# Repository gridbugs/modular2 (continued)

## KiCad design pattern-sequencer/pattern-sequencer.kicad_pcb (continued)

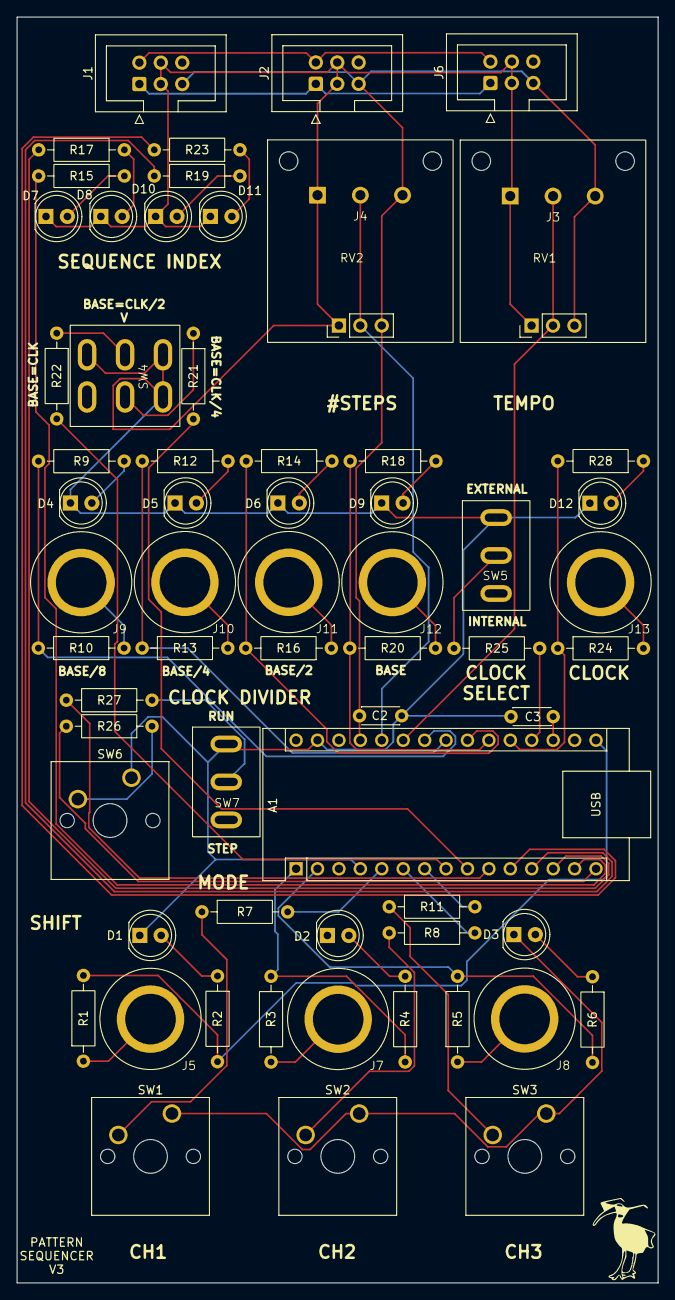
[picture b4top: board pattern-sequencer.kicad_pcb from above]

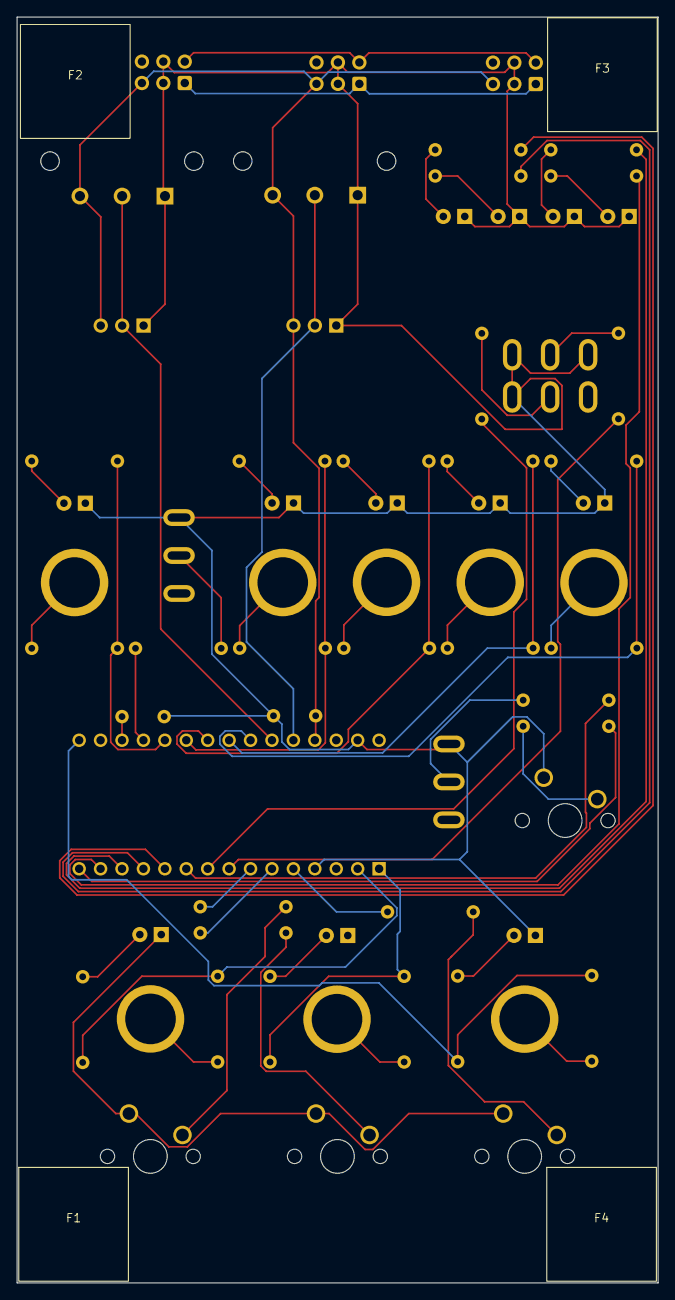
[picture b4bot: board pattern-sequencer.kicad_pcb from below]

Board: 2 copper layers, 76.0 x 150.1 mm, 69 parts (4 on the bottom side), 55 nets.

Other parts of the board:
F1, F2, F3, F4: foot

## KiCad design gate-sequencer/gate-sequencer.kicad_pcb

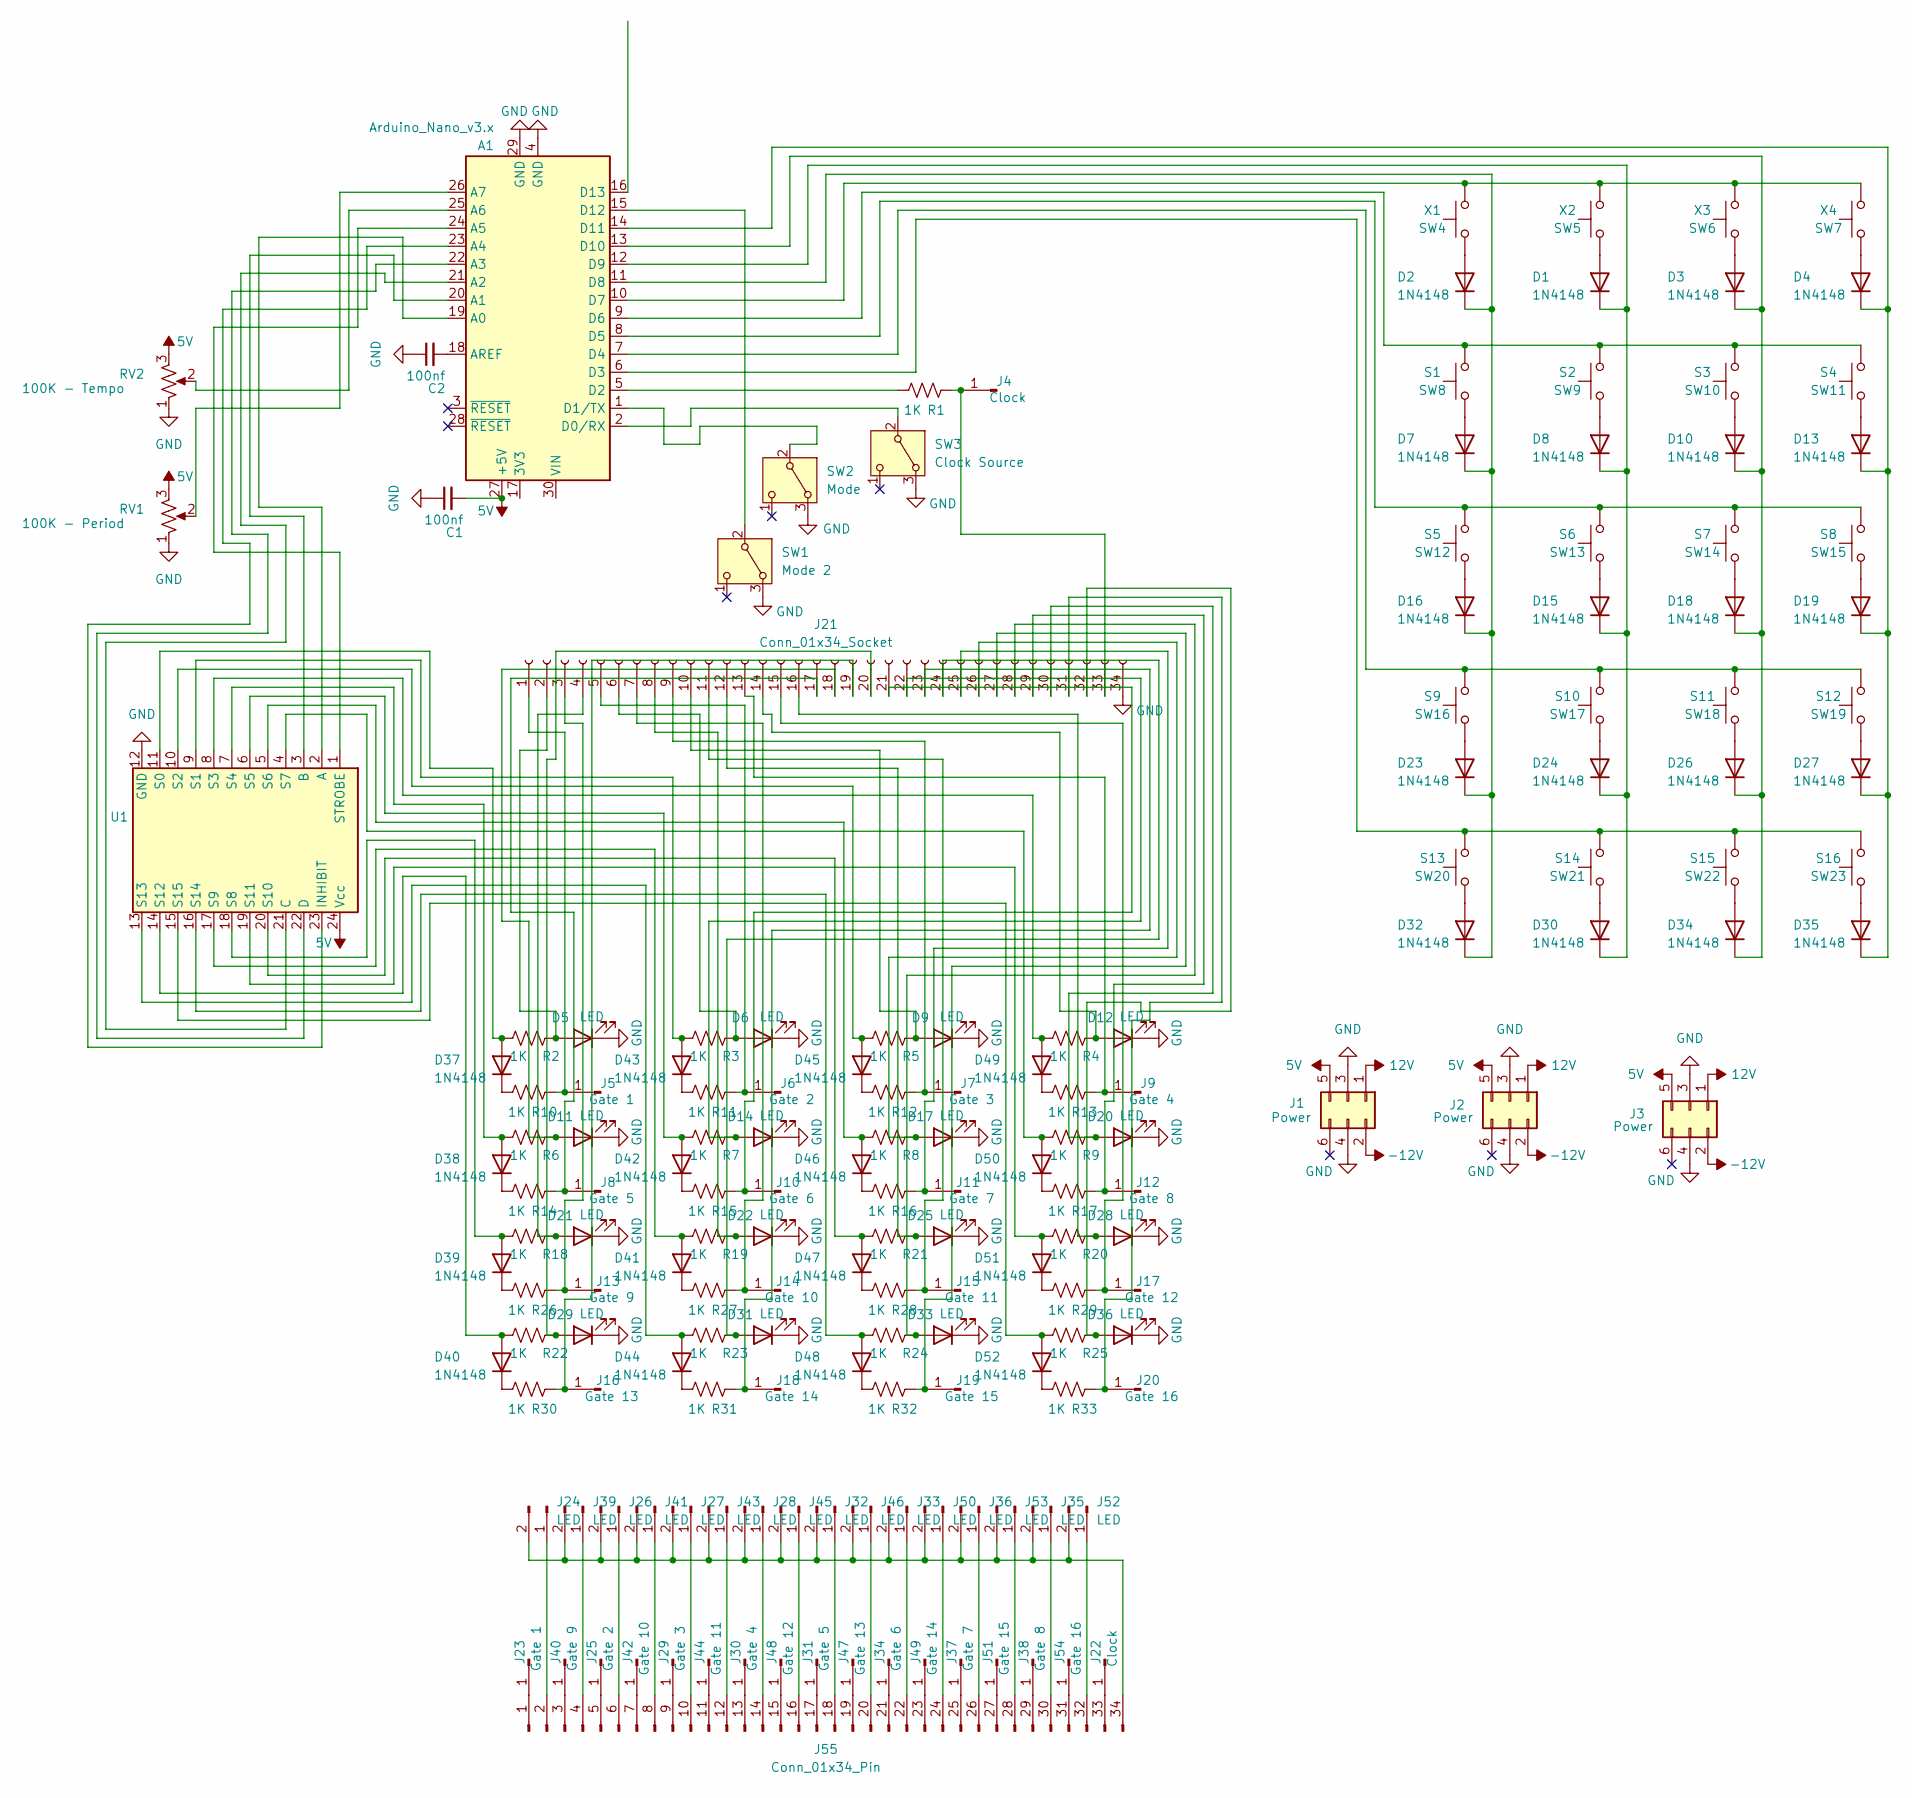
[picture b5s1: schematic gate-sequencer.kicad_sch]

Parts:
A1: Arduino_Nano_v3.x; Arduino_Nano
C1, C2: 100nf; C_Disc_D4.3mm_W1.9mm_P5.00mm
D1, D2, D3, D4, D7, D8, D10, D13, D15, D16, D18, D19, D23, D24, D26, D27, D30, D32, D34, D35, D37, D38, D39, D40, D41, D42, D43, D44, D45, D46, D47, D48, D49, D50, D51, D52: 1N4148; D_DO-35_SOD27_P7.62mm_Horizontal
D5, D6, D9, D11, D12, D14, D17, D20, D21, D22, D25, D28, D29, D31, D33, D36: LED; LED_D5.0mm
J1, J2, J3: Power; IDC-Header_2x03_P2.54mm_Vertical
J4, J22: Clock; banana-jack
J5, J23: Gate 1; banana-jack
J6, J25: Gate 2; banana-jack
J7, J29: Gate 3; banana-jack
J8, J31: Gate 5; banana-jack
J9, J30: Gate 4; banana-jack
J10, J34: Gate 6; banana-jack
J11, J37: Gate 7; banana-jack
J12, J38: Gate 8; banana-jack
J13, J40: Gate 9; banana-jack
J14, J42: Gate 10; banana-jack
J15, J44: Gate 11; banana-jack
J16, J47: Gate 13; banana-jack
J17, J48: Gate 12; banana-jack
J18, J49: Gate 14; banana-jack
J19, J51: Gate 15; banana-jack
J20, J54: Gate 16; banana-jack
J21: Conn_01x34_Socket; PinSocket_1x34_P2.54mm_Vertical
J24, J26, J27, J28, J32, J33, J35, J36, J39, J41, J43, J45, J46, J50, J52, J53: LED; PinHeader_1x02_P2.54mm_Vertical
J55: Conn_01x34_Pin; PinHeader_1x34_P2.54mm_Vertical
R1, R2, R3, R4, R5, R6, R7, R8, R9, R10, R11, R12, R13, R14, R15, R16, R17, R18, R19, R20, R21, R22, R23, R24, R25, R26, R27, R28, R29, R30, R31, R32, R33: 1K; R_Axial_DIN0207_L6.3mm_D2.5mm_P10.16mm_Horizontal
RV1: 100K - Period; Potentiometer_Alps_RK09K_Single_Vertical
RV2: 100K - Tempo; Potentiometer_Alps_RK09K_Single_Vertical
SW1: Mode 2; switch1
SW2: Mode; switch1
SW3: Clock Source; switch1
SW4: X1; SW_Cherry_MX_1.00u_PCB
SW5: X2; SW_Cherry_MX_1.00u_PCB
SW6: X3; SW_Cherry_MX_1.00u_PCB
SW7: X4; SW_Cherry_MX_1.00u_PCB
SW8: S1; SW_Cherry_MX_1.00u_PCB
SW9: S2; SW_Cherry_MX_1.00u_PCB
SW10: S3; SW_Cherry_MX_1.00u_PCB
SW11: S4; SW_Cherry_MX_1.00u_PCB
SW12: S5; SW_Cherry_MX_1.00u_PCB
SW13: S6; SW_Cherry_MX_1.00u_PCB
SW14: S7; SW_Cherry_MX_1.00u_PCB
SW15: S8; SW_Cherry_MX_1.00u_PCB
SW16: S9; SW_Cherry_MX_1.00u_PCB
SW17: S10; SW_Cherry_MX_1.00u_PCB
SW18: S11; SW_Cherry_MX_1.00u_PCB
SW19: S12; SW_Cherry_MX_1.00u_PCB
SW20: S13; SW_Cherry_MX_1.00u_PCB
SW21: S14; SW_Cherry_MX_1.00u_PCB
SW22: S15; SW_Cherry_MX_1.00u_PCB
SW23: S16; SW_Cherry_MX_1.00u_PCB
U1: DIP-24_W7.62mm_Socket

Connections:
5V: A1.27 (+5V), C1.2, J1.5, J2.5, J3.5, RV1.3, RV2.3, U1.24 (Vcc)
12V: J1.1, J2.1, J3.1
-12V: J1.2, J2.2, J3.2
GND: A1.4 (GND), A1.29 (GND), C1.1, C2.1, D5.1 (K), D6.1 (K), D9.1 (K), D11.1 (K), D12.1 (K), D14.1 (K), D17.1 (K), D20.1 (K), D21.1 (K), D22.1 (K), D25.1 (K), D28.1 (K), D29.1 (K), D31.1 (K), D33.1 (K), D36.1 (K), J1.3, J1.4, J2.3, J2.4, J3.3, J3.4, J21.34, RV1.1, RV2.1, SW1.3 (A), SW2.3 (A), SW3.3 (A), U1.12 (GND)
unnamed: A1.19 (A0), U1.2 (A)
unnamed: A1.20 (A1), U1.3 (B)
unnamed: A1.21 (A2), U1.21 (C)
unnamed: A1.22 (A3), U1.22 (D)
unnamed: A1.23 (A4), U1.23 (INHIBIT)
unnamed: A1.24 (A5), U1.1 (STROBE)
unnamed: A1.25 (A6), RV2.2
unnamed: A1.26 (A7), RV1.2
unnamed: A1.18 (AREF), C2.2
unnamed: A1.2 (D0/RX), SW3.2 (B)
unnamed: A1.1 (D1/TX), SW2.2 (B)
unnamed: A1.5 (D2), R1.2
unnamed: A1.6 (D3), SW20.2, SW21.2, SW22.2, SW23.2
unnamed: A1.7 (D4), SW16.2, SW17.2, SW18.2, SW19.2
unnamed: A1.8 (D5), SW12.2, SW13.2, SW14.2, SW15.2
unnamed: A1.9 (D6), SW8.2, SW9.2, SW10.2, SW11.2
unnamed: A1.10 (D7), SW4.2, SW5.2, SW6.2, SW7.2
unnamed: A1.11 (D8), D2.1 (K), D7.1 (K), D16.1 (K), D23.1 (K), D32.1 (K)
unnamed: A1.12 (D9), D1.1 (K), D8.1 (K), D15.1 (K), D24.1 (K), D30.1 (K)
unnamed: A1.13 (D10), D3.1 (K), D10.1 (K), D18.1 (K), D26.1 (K), D34.1 (K)
unnamed: A1.14 (D11), D4.1 (K), D13.1 (K), D19.1 (K), D27.1 (K), D35.1 (K)
unnamed: A1.15 (D12), SW1.2 (B)
unnamed: D1.2 (A), SW5.1
unnamed: D2.2 (A), SW4.1
unnamed: D3.2 (A), SW6.1
unnamed: D4.2 (A), SW7.1
unnamed: D5.2 (A), J21.2, R2.1
unnamed: D6.2 (A), J21.6, R3.1
unnamed: D7.2 (A), SW8.1
unnamed: D8.2 (A), SW9.1
unnamed: D9.2 (A), J21.10, R5.1
unnamed: D10.2 (A), SW10.1
unnamed: D11.2 (A), J21.18, R6.1
unnamed: D12.2 (A), J21.14, R4.1
unnamed: D13.2 (A), SW11.1
unnamed: D14.2 (A), J21.22, R7.1
unnamed: D15.2 (A), SW13.1
unnamed: D16.2 (A), SW12.1
unnamed: D17.2 (A), J21.26, R8.1
unnamed: D18.2 (A), SW14.1
unnamed: D19.2 (A), SW15.1
unnamed: D20.2 (A), J21.30, R9.1
unnamed: D21.2 (A), J21.4, R18.1
unnamed: D22.2 (A), J21.8, R19.1
unnamed: D23.2 (A), SW16.1
unnamed: D24.2 (A), SW17.1
unnamed: D25.2 (A), J21.12, R21.1
unnamed: D26.2 (A), SW18.1
unnamed: D27.2 (A), SW19.1
unnamed: D28.2 (A), J21.16, R20.1
unnamed: D29.2 (A), J21.20, R22.1
unnamed: D30.2 (A), SW21.1
unnamed: D31.2 (A), J21.24, R23.1
unnamed: D32.2 (A), SW20.1
unnamed: D33.2 (A), J21.28, R24.1
unnamed: D34.2 (A), SW22.1
unnamed: D35.2 (A), SW23.1
unnamed: D36.2 (A), J21.32, R25.1
unnamed: D37.2 (A), R2.2, U1.11 (S0)
unnamed: D37.1 (K), R10.2
unnamed: D38.2 (A), R6.2, U1.7 (S4)
unnamed: D38.1 (K), R14.2
unnamed: D39.2 (A), R18.2, U1.18 (S8)
unnamed: D39.1 (K), R26.2
unnamed: D40.2 (A), R22.2, U1.14 (S12)
unnamed: D40.1 (K), R30.2
unnamed: D41.2 (A), R19.2, U1.17 (S9)
unnamed: D41.1 (K), R27.2
unnamed: D42.2 (A), R7.2, U1.6 (S5)
unnamed: D42.1 (K), R15.2
unnamed: D43.2 (A), R3.2, U1.9 (S1)
unnamed: D43.1 (K), R11.2
unnamed: D44.2 (A), R23.2, U1.13 (S13)
unnamed: D44.1 (K), R31.2
unnamed: D45.2 (A), R5.2, U1.10 (S2)
unnamed: D45.1 (K), R12.2
unnamed: D46.2 (A), R8.2, U1.5 (S6)
unnamed: D46.1 (K), R16.2
unnamed: D47.2 (A), R21.2, U1.20 (S10)
unnamed: D47.1 (K), R28.2
unnamed: D48.2 (A), R24.2, U1.16 (S14)
unnamed: D48.1 (K), R32.2
unnamed: D49.2 (A), R4.2, U1.8 (S3)
unnamed: D49.1 (K), R13.2
unnamed: D50.2 (A), R9.2, U1.4 (S7)
unnamed: D50.1 (K), R17.2
unnamed: D51.2 (A), R20.2, U1.19 (S11)
unnamed: D51.1 (K), R29.2
unnamed: D52.2 (A), R25.2, U1.15 (S15)
unnamed: D52.1 (K), R33.2
unnamed: J10.1 (Pin_1_1), J21.21, R15.1
unnamed: J11.1 (Pin_1_1), J21.25, R16.1
unnamed: J12.1 (Pin_1_1), J21.29, R17.1
unnamed: J13.1 (Pin_1_1), J21.3, R26.1
unnamed: J14.1 (Pin_1_1), J21.7, R27.1
unnamed: J15.1 (Pin_1_1), J21.11, R28.1
unnamed: J16.1 (Pin_1_1), J21.19, R30.1
unnamed: J17.1 (Pin_1_1), J21.15, R29.1
unnamed: J18.1 (Pin_1_1), J21.23, R31.1
unnamed: J19.1 (Pin_1_1), J21.27, R32.1
unnamed: J20.1 (Pin_1_1), J21.31, R33.1
unnamed: J5.1 (Pin_1_1), J21.1, R10.1
unnamed: J6.1 (Pin_1_1), J21.5, R11.1
unnamed: J7.1 (Pin_1_1), J21.9, R12.1
unnamed: J9.1 (Pin_1_1), J21.13, R13.1
unnamed: J8.1 (Pin_1_1), J21.17, R14.1
unnamed: J4.1 (Pin_1_1), J21.33, R1.1
unnamed: J22.1 (Pin_1_1), J55.33
unnamed: J23.1 (Pin_1_1), J55.1
unnamed: J24.1, J55.2
unnamed: J24.2, J26.2, J27.2, J28.2, J32.2, J33.2, J35.2, J36.2, J39.2, J41.2, J43.2, J45.2, J46.2, J50.2, J52.2, J53.2, J55.34
unnamed: J25.1 (Pin_1_1), J55.5
unnamed: J26.1, J55.6
unnamed: J27.1, J55.10
unnamed: J28.1, J55.14
unnamed: J29.1 (Pin_1_1), J55.9
unnamed: J30.1 (Pin_1_1), J55.13
unnamed: J31.1 (Pin_1_1), J55.17
unnamed: J32.1, J55.18
unnamed: J33.1, J55.22
unnamed: J34.1 (Pin_1_1), J55.21
unnamed: J35.1, J55.30
unnamed: J36.1, J55.26
unnamed: J37.1 (Pin_1_1), J55.25
unnamed: J38.1 (Pin_1_1), J55.29
unnamed: J39.1, J55.4
unnamed: J40.1 (Pin_1_1), J55.3
unnamed: J41.1, J55.8
unnamed: J42.1 (Pin_1_1), J55.7
unnamed: J43.1, J55.12
unnamed: J44.1 (Pin_1_1), J55.11
unnamed: J45.1, J55.16
unnamed: J46.1, J55.20
unnamed: J47.1 (Pin_1_1), J55.19
unnamed: J48.1 (Pin_1_1), J55.15
unnamed: J49.1 (Pin_1_1), J55.23
unnamed: J50.1, J55.24
unnamed: J51.1 (Pin_1_1), J55.27
unnamed: J52.1, J55.32
unnamed: J53.1, J55.28
unnamed: J54.1 (Pin_1_1), J55.31

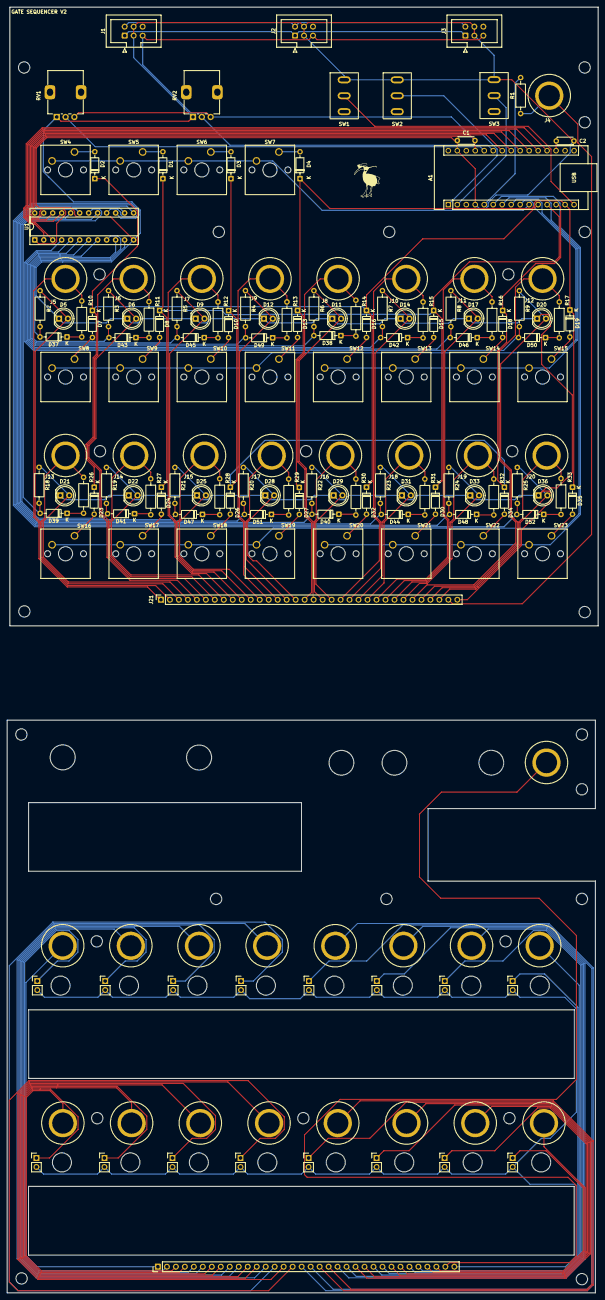
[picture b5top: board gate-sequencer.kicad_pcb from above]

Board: 2 copper layers, 167.1 x 363.5 mm, 169 parts (0 on the bottom side), 145 nets.

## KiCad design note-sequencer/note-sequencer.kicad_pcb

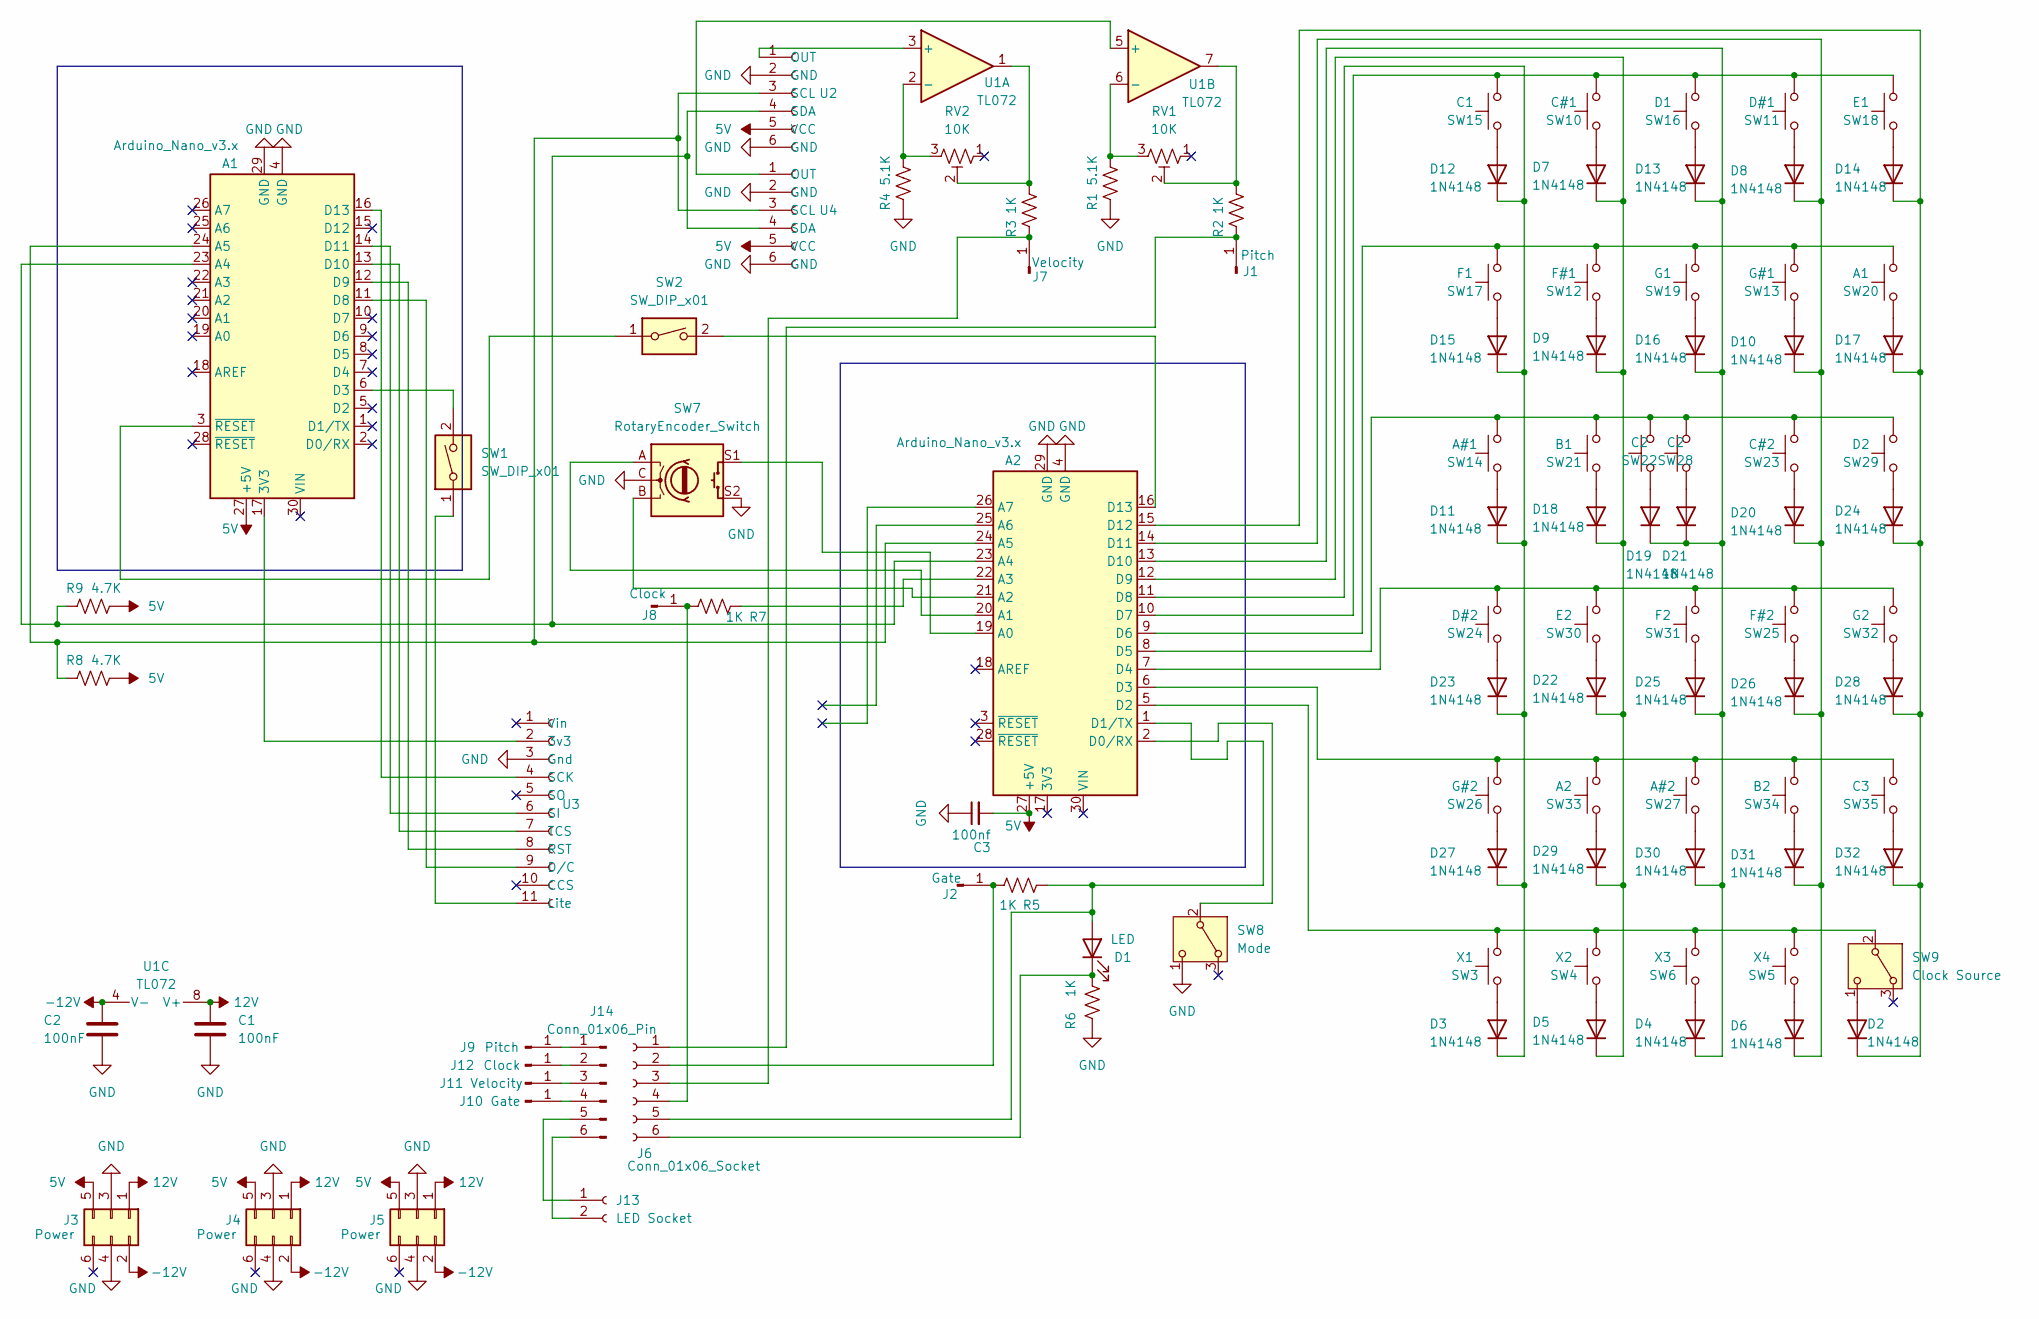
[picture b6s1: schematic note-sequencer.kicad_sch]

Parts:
A1, A2: Arduino_Nano_v3.x; Arduino_Nano
C1, C2: 100nF; C_Disc_D4.3mm_W1.9mm_P5.00mm
C3: 100nf; C_Disc_D4.3mm_W1.9mm_P5.00mm
D1: LED; LED_D5.0mm
D2, D3, D4, D5, D6, D7, D8, D9, D10, D11, D12, D13, D14, D15, D16, D17, D18, D19, D20, D21, D22, D23, D24, D25, D26, D27, D28, D29, D30, D31, D32: 1N4148; D_DO-35_SOD27_P7.62mm_Horizontal
J1, J9: Pitch; banana-jack
J2, J10: Gate; banana-jack
J3, J4, J5: Power; IDC-Header_2x03_P2.54mm_Vertical
J6: Conn_01x06_Socket; PinSocket_1x06_P2.54mm_Vertical
J7, J11: Velocity; banana-jack
J8, J12: Clock; banana-jack
J13: LED Socket; PinHeader_1x02_P2.54mm_Vertical
J14: Conn_01x06_Pin; PinHeader_1x06_P2.54mm_Vertical
R1, R4: 5.1K; R_Axial_DIN0207_L6.3mm_D2.5mm_P10.16mm_Horizontal
R2, R3, R5, R6, R7: 1K; R_Axial_DIN0207_L6.3mm_D2.5mm_P10.16mm_Horizontal
R8, R9: 4.7K; R_Axial_DIN0207_L6.3mm_D2.5mm_P10.16mm_Horizontal
RV1, RV2: 10K; Potentiometer_Bourns_3296W_Vertical
SW1, SW2: SW_DIP_x01; SW_DIP_SPSTx01_Slide_9.78x4.72mm_W7.62mm_P2.54mm
SW3: X1; SW_Cherry_MX_1.00u_PCB
SW4: X2; SW_Cherry_MX_1.00u_PCB
SW5: X4; SW_Cherry_MX_1.00u_PCB
SW6: X3; SW_Cherry_MX_1.00u_PCB
SW7: RotaryEncoder_Switch; RotaryEncoder_Alps_EC11E-Switch_Vertical_H20mm
SW8: Mode; switch1
SW9: Clock Source; switch1
SW10: C#1; SW_Cherry_MX_1.00u_PCB
SW11: D#1; SW_Cherry_MX_1.00u_PCB
SW12: F#1; SW_Cherry_MX_1.00u_PCB
SW13: G#1; SW_Cherry_MX_1.00u_PCB
SW14: A#1; SW_Cherry_MX_1.00u_PCB
SW15: C1; SW_Cherry_MX_1.00u_PCB
SW16: D1; SW_Cherry_MX_1.00u_PCB
SW17: F1; SW_Cherry_MX_1.00u_PCB
SW18: E1; SW_Cherry_MX_1.00u_PCB
SW19: G1; SW_Cherry_MX_1.00u_PCB
SW20: A1; SW_Cherry_MX_1.00u_PCB
SW21: B1; SW_Cherry_MX_1.00u_PCB
SW22, SW28: C2; SW_Cherry_MX_1.00u_PCB
SW23: C#2; SW_Cherry_MX_1.00u_PCB
SW24: D#2; SW_Cherry_MX_1.00u_PCB
SW25: F#2; SW_Cherry_MX_1.00u_PCB
SW26: G#2; SW_Cherry_MX_1.00u_PCB
SW27: A#2; SW_Cherry_MX_1.00u_PCB
SW29: D2; SW_Cherry_MX_1.00u_PCB
SW30: E2; SW_Cherry_MX_1.00u_PCB
SW31: F2; SW_Cherry_MX_1.00u_PCB
SW32: G2; SW_Cherry_MX_1.00u_PCB
SW33: A2; SW_Cherry_MX_1.00u_PCB
SW34: B2; SW_Cherry_MX_1.00u_PCB
SW35: C3; SW_Cherry_MX_1.00u_PCB
U1: TL072; DIP-8_W7.62mm_Socket
U2, U4: mcp4725_breakout
U3: st7735

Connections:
5V: A1.27 (+5V), A2.27 (+5V), C3.2, J3.5, J4.5, J5.5, R8.2, R9.2, U2.5 (VCC), U4.5 (VCC)
12V: C1.2, J3.1, J4.1, J5.1, U1.8 (V+)
-12V: C2.2, J3.2, J4.2, J5.2, U1.4 (V-)
GND: A1.4 (GND), A1.29 (GND), A2.4 (GND), A2.29 (GND), C1.1, C2.1, C3.1, J3.3, J3.4, J4.3, J4.4, J5.3, J5.4, R1.1, R4.1, R6.1, SW7.C, SW7.S2, SW8.1 (C), U2.2 (GND), U2.6 (GND), U3.3 (Gnd), U4.2 (GND), U4.6 (GND)
unnamed: A1.17 (3V3), U3.2 (3v3)
unnamed: A1.23 (A4), A2.23 (A4), R9.1, U2.4 (SDA), U4.4 (SDA)
unnamed: A1.24 (A5), A2.24 (A5), R8.1, U2.3 (SCL), U4.3 (SCL)
unnamed: A1.6 (D3), SW1.2
unnamed: A1.11 (D8), U3.9 (D/C)
unnamed: A1.12 (D9), U3.8 (RST)
unnamed: A1.13 (D10), U3.7 (TCS)
unnamed: A1.14 (D11), U3.6 (SI)
unnamed: A1.16 (D13), U3.4 (SCK)
unnamed: A1.3 (~RESET), SW2.1
unnamed: A2.19 (A0), SW7.S1
unnamed: A2.20 (A1), SW7.A
unnamed: A2.21 (A2), SW7.B
unnamed: A2.22 (A3), R7.1
unnamed: A2.2 (D0/RX), SW8.2 (B)
unnamed: A2.1 (D1/TX), D1.2 (A), J6.5, R5.1
unnamed: A2.5 (D2), SW3.2, SW4.2, SW5.2, SW6.2, SW9.2 (B)
unnamed: A2.6 (D3), SW26.2, SW27.2, SW33.2, SW34.2, SW35.2
unnamed: A2.7 (D4), SW24.2, SW25.2, SW30.2, SW31.2, SW32.2
unnamed: A2.8 (D5), SW14.2, SW21.2, SW22.2, SW23.2, SW28.2, SW29.2
unnamed: A2.9 (D6), SW12.2, SW13.2, SW17.2, SW19.2, SW20.2
unnamed: A2.10 (D7), SW10.2, SW11.2, SW15.2, SW16.2, SW18.2
unnamed: A2.11 (D8), D3.1 (K), D11.1 (K), D12.1 (K), D15.1 (K), D23.1 (K), D27.1 (K)
unnamed: A2.12 (D9), D5.1 (K), D7.1 (K), D9.1 (K), D18.1 (K), D22.1 (K), D29.1 (K)
unnamed: A2.13 (D10), D4.1 (K), D13.1 (K), D16.1 (K), D19.1 (K), D21.1 (K), D25.1 (K), D30.1 (K)
unnamed: A2.14 (D11), D6.1 (K), D8.1 (K), D10.1 (K), D20.1 (K), D26.1 (K), D31.1 (K)
unnamed: A2.15 (D12), D2.1 (K), D14.1 (K), D17.1 (K), D24.1 (K), D28.1 (K), D32.1 (K)
unnamed: A2.16 (D13), SW2.2
unnamed: D1.1 (K), J6.6, R6.2
unnamed: D2.2 (A), SW9.1 (C)
unnamed: D3.2 (A), SW3.1
unnamed: D4.2 (A), SW6.1
unnamed: D5.2 (A), SW4.1
unnamed: D6.2 (A), SW5.1
unnamed: D7.2 (A), SW10.1
unnamed: D8.2 (A), SW11.1
unnamed: D9.2 (A), SW12.1
unnamed: D10.2 (A), SW13.1
unnamed: D11.2 (A), SW14.1
unnamed: D12.2 (A), SW15.1
unnamed: D13.2 (A), SW16.1
unnamed: D14.2 (A), SW18.1
unnamed: D15.2 (A), SW17.1
unnamed: D16.2 (A), SW19.1
unnamed: D17.2 (A), SW20.1
unnamed: D18.2 (A), SW21.1
unnamed: D19.2 (A), SW22.1
unnamed: D20.2 (A), SW23.1
unnamed: D21.2 (A), SW28.1
unnamed: D22.2 (A), SW30.1
unnamed: D23.2 (A), SW24.1
unnamed: D24.2 (A), SW29.1
unnamed: D25.2 (A), SW31.1
unnamed: D26.2 (A), SW25.1
unnamed: D27.2 (A), SW26.1
unnamed: D28.2 (A), SW32.1
unnamed: D29.2 (A), SW33.1
unnamed: D30.2 (A), SW27.1
unnamed: D31.2 (A), SW34.1
unnamed: D32.2 (A), SW35.1
unnamed: J1.1, J6.1, R2.1
unnamed: J2.1, J6.2, R5.2
unnamed: J6.3, J7.1, R3.1
unnamed: J6.4, J8.1, R7.2
unnamed: J10.1, J14.4
unnamed: J11.1, J14.3
unnamed: J12.1, J14.2
unnamed: J13.1, J14.5
unnamed: J13.2, J14.6
unnamed: J9.1, J14.1
unnamed: R2.2, RV1.2, U1.7
unnamed: R3.2, RV2.2, U1.1
unnamed: U1.3 (+), U2.1 (OUT)
unnamed: R4.2, RV2.3, U1.2 (-)
unnamed: U1.5 (+), U4.1 (OUT)
unnamed: R1.2, RV1.3, U1.6 (-)
unnamed: SW1.1, U3.11 (Lite)

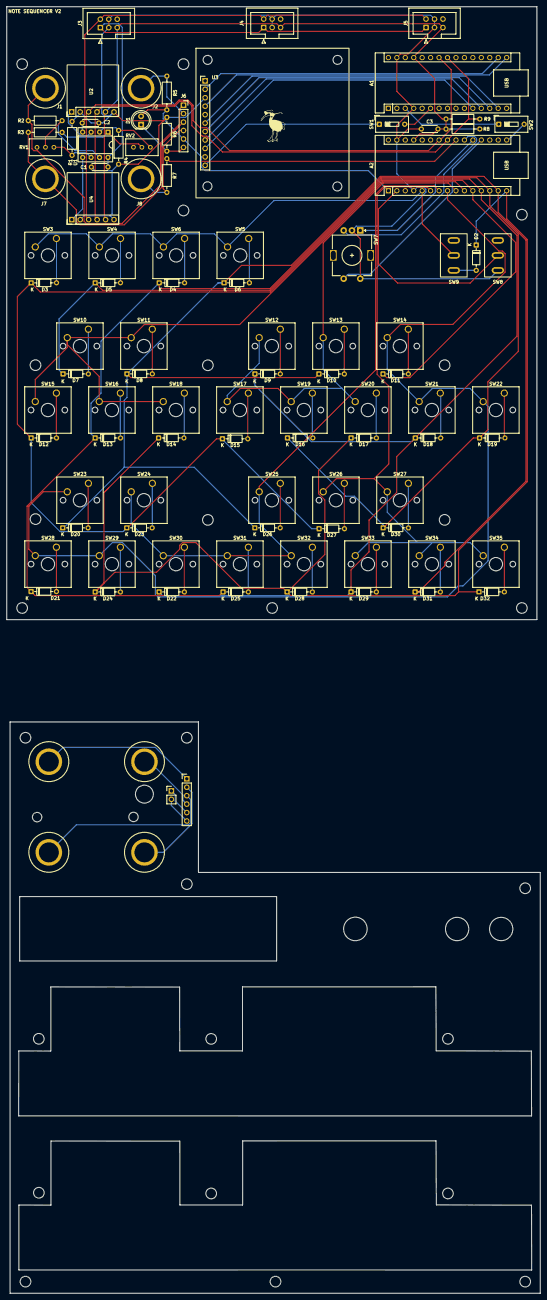
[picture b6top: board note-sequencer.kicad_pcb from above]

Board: 2 copper layers, 159.4 x 184.2 mm, 101 parts (0 on the bottom side), 81 nets.

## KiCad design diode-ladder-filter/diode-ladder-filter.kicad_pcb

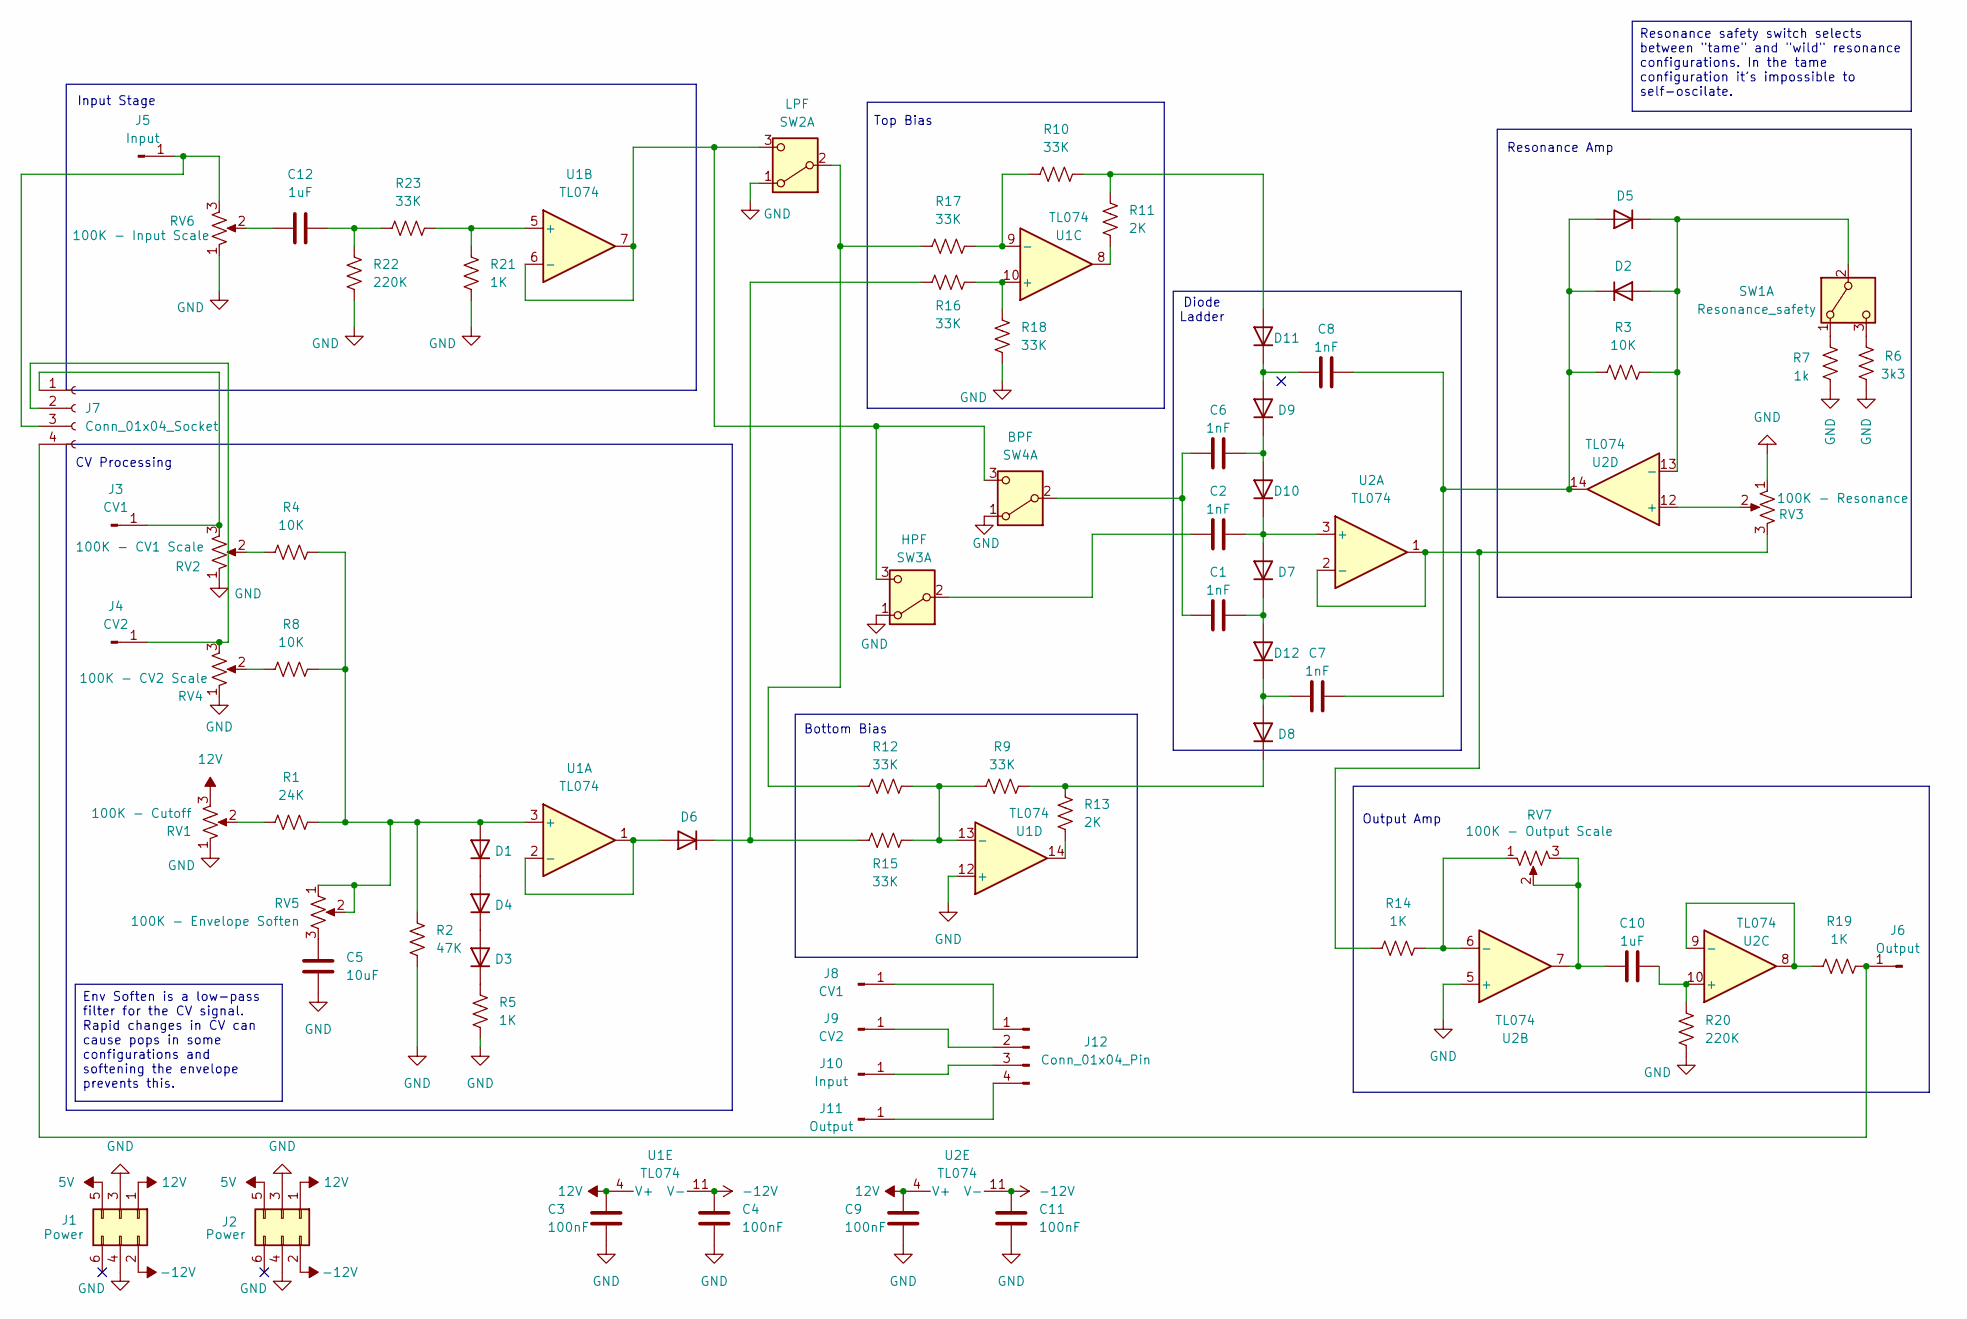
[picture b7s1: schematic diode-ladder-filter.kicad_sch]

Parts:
C1, C2, C6, C7, C8: 1nF; C_Disc_D4.3mm_W1.9mm_P5.00mm
C3, C4, C9, C11: 100nF; C_Disc_D4.3mm_W1.9mm_P5.00mm
C5: 10uF; C_Disc_D4.3mm_W1.9mm_P5.00mm
C10, C12: 1uF; C_Disc_D4.3mm_W1.9mm_P5.00mm
D1, D2, D3, D4, D5, D6, D7, D8, D9, D10, D11, D12: D; D_A-405_P7.62mm_Horizontal
J1, J2: Power; IDC-Header_2x03_P2.54mm_Vertical
J3, J8: CV1; banana-jack
J4, J9: CV2; banana-jack
J5, J10: Input; banana-jack
J6, J11: Output; banana-jack
J7: Conn_01x04_Socket; PinSocket_1x04_P2.54mm_Vertical
J12: Conn_01x04_Pin; PinHeader_1x04_P2.54mm_Vertical
R1: 24K; R_Axial_DIN0207_L6.3mm_D2.5mm_P10.16mm_Horizontal
R2: 47K; R_Axial_DIN0207_L6.3mm_D2.5mm_P10.16mm_Horizontal
R3, R4, R8: 10K; R_Axial_DIN0207_L6.3mm_D2.5mm_P10.16mm_Horizontal
R5, R14, R19, R21: 1K; R_Axial_DIN0207_L6.3mm_D2.5mm_P10.16mm_Horizontal
R6: 3k3; R_Axial_DIN0207_L6.3mm_D2.5mm_P10.16mm_Horizontal
R7: 1k; R_Axial_DIN0207_L6.3mm_D2.5mm_P10.16mm_Horizontal
R9, R10, R12, R15, R16, R17, R18, R23: 33K; R_Axial_DIN0207_L6.3mm_D2.5mm_P10.16mm_Horizontal
R11, R13: 2K; R_Axial_DIN0207_L6.3mm_D2.5mm_P10.16mm_Horizontal
R20, R22: 220K; R_Axial_DIN0207_L6.3mm_D2.5mm_P10.16mm_Horizontal
RV1: 100K - Cutoff; Potentiometer_Alps_RK09K_Single_Vertical
RV2: 100K - CV1 Scale; Potentiometer_Alps_RK09K_Single_Vertical
RV3: 100K - Resonance; Potentiometer_Alps_RK09K_Single_Vertical
RV4: 100K - CV2 Scale; Potentiometer_Alps_RK09K_Single_Vertical
RV5: 100K - Envelope Soften; Potentiometer_Alps_RK09K_Single_Vertical
RV6: 100K - Input Scale; Potentiometer_Alps_RK09K_Single_Vertical
RV7: 100K - Output Scale; Potentiometer_Alps_RK09K_Single_Vertical
SW1: Resonance_safety; switch1
SW2: LPF; switch1
SW3: HPF; switch1
SW4: BPF; switch1
U1, U2: TL074; DIP-14_W7.62mm_Socket

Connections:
5V: J1.5, J2.5
12V: C3.2, C9.2, J1.1, J2.1, RV1.3, U1.4 (V+), U2.4 (V+)
-12V: C4.2, C11.2, J1.2, J2.2, U1.11 (V-), U2.11 (V-)
GND: C3.1, C4.1, C5.1, C9.1, C11.1, J1.3, J1.4, J2.3, J2.4, R2.1, R5.1, R6.1, R7.1, R18.1, R20.2, R21.2, R22.2, RV1.1, RV2.1, RV3.1, RV4.1, RV6.1, SW2.1 (A), SW3.1 (A), SW4.1 (A), U1.12 (+), U2.5 (+)
unnamed: C5.2, RV5.3
unnamed: C10.1, RV7.2, RV7.3, U2.7
unnamed: C12.1, RV6.2
unnamed: C12.2, R22.1, R23.1
unnamed: D1.2 (A), R1.1, R2.2, R4.1, R8.1, RV5.1, RV5.2, U1.3 (+)
unnamed: D1.1 (K), D4.2 (A)
unnamed: D2.2 (A), D5.1 (K), R3.2, SW1.2 (B), U2.13 (-)
unnamed: C7.2, C8.2, D2.1 (K), D5.2 (A), R3.1, U2.14
unnamed: D3.2 (A), D4.1 (K)
unnamed: D3.1 (K), R5.2
unnamed: D6.2 (A), U1.1, U1.2 (-)
unnamed: D6.1 (K), R15.2, R16.2
unnamed: D8.1 (K), R9.1, R13.2
unnamed: C6.2, D9.1 (K), D10.2 (A)
unnamed: C2.2, D7.2 (A), D10.1 (K), U2.3 (+)
unnamed: D11.2 (A), R10.2, R11.2
unnamed: C8.1, D9.2 (A), D11.1 (K)
unnamed: C1.2, D7.1 (K), D12.2 (A)
unnamed: C7.1, D8.2 (A), D12.1 (K)
unnamed: J3.1, J7.1, RV2.3
unnamed: J4.1, J7.2, RV4.3
unnamed: J5.1, J7.3, RV6.3
unnamed: J6.1, J7.4, R19.2
unnamed: J10.1, J12.3
unnamed: J11.1, J12.4
unnamed: J8.1, J12.1
unnamed: J9.1, J12.2
unnamed: R1.2, RV1.2
unnamed: R4.2, RV2.2
unnamed: R8.2, RV4.2
unnamed: R11.1, U1.8
unnamed: R13.1, U1.14
unnamed: R7.2, SW1.1 (A)
unnamed: R6.2, SW1.3 (C)
unnamed: R12.2, R17.1, SW2.2 (B)
unnamed: SW2.3 (C), SW3.3 (C), SW4.3 (C), U1.6 (-), U1.7
unnamed: C2.1, SW3.2 (B)
unnamed: C1.1, C6.1, SW4.2 (B)
unnamed: R21.1, R23.2, U1.5 (+)
unnamed: R16.1, R18.2, U1.10 (+)
unnamed: R10.1, R17.2, U1.9 (-)
unnamed: R9.2, R12.1, R15.1, U1.13 (-)
unnamed: R14.1, RV3.3, U2.1, U2.2 (-)
unnamed: R14.2, RV7.1, U2.6 (-)
unnamed: C10.2, R20.1, U2.10 (+)
unnamed: R19.1, U2.8, U2.9 (-)
unnamed: RV3.2, U2.12 (+)

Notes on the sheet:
Bottom Bias
Resonance Amp
Input Stage
Output Amp
Top Bias
Diode Ladder
CV Processing
Resonance safety switch selects between "tame" and "wild" resonance configurations. In the tame configuration it's impossible to self-oscilate.
Env Soften is a low-pass filter for the CV signal. Rapid changes in CV can cause pops in some configurations and softening the envelope prevents this.
